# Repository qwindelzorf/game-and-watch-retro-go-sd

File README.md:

# Nintendo® Game & Watch™ Retro-Go SD

A comprehensive emulator collection for the Nintendo® Game & Watch™ with SD Card support, allowing you to play your favorite retro games on the go!

## Table of Contents
- [Support Development](#support-development)
- [Features](#features)
- [SD Card KiCad Project]
- [Installation](#installation)
  - [Pre-modded Options](#pre-modded-options)
  - [Hardware Requirements](#hardware-requirements)
  - [Installation Steps](#installation-steps)
  - [Shell Replacement](#shell-replacement)
  - [Retro-Go-SD Update Steps](#retro-go-sd-update-steps)
- [Supported Systems](#supported-systems)
  - [Emulators](#emulators)
  - [SNES Ports](#snes-ports)
  - [Homebrew Ports](#homebrew-ports)
- [Controls](#controls)
  - [Button Mappings](#button-mappings)
  - [Macros](#macros)
- [Troubleshooting / FAQ](#troubleshooting--faq)
- [Cheat Codes](#cheat-codes)
  - [Cheat codes on NES System](#cheat-codes-on-nes-system)
  - [Cheat codes on GB System](#cheat-codes-on-gb-system)
  - [Cheat codes on PCE System](#cheat-codes-on-pce-system)
  - [Cheat codes on MSX System](#cheat-codes-on-msx-system)
- [NES Emulator](#nes-emulator)
- [MSX Emulator](#msx-emulator)
- [Amstrad CPC6128 Emulator](#amstrad-cpc6128-emulator)
- [Pokémon Mini Emulator](#pokémon-mini-emulator)
- [Homebrew ports](#homebrew-ports)
  - [The Legend of Zelda: A Link to the Past](#the-legend-of-zelda-a-link-to-the-past)
    - [Alternate languages](#alternate-languages)
  - [Super Mario World](#super-mario-world)
  - [Celeste Classic](#celeste-classic)
- [Discord, support and discussion](#discord-support-and-discussion)
- [License](#license)

## Support Development

You can support the development by donating via [PayPal](https://paypal.me/revlys)

## Features

- 🎮 Support for multiple retro gaming systems
- 💾 SD Card storage for ROMs and games
- 💾 4 save state slots per game
- 🎨 Cover art support
- 🔄 Easy firmware updates
- 🌐 Unicode support (Latin and Cyrillic, more to come)
- 🎯 Cheat code support for multiple systems
- 🔄 Dual boot capability (original firmware preservation)

Current limitations :
- Up to 1000 roms/disks will be visible for each system
- CJK characters not yet visible

## SD Card KiCad Project

This is a remake of the original GnW SD Adapter based on the gerbers from the [upstream repo](https://github.com/sylverb/game-and-watch-retro-go-sd/raw/refs/heads/main/assets/GnW_SD_v2.zip). Parts have been changed and the board redesigned for easy production from JLCpcb. 
Credits to Tim Schuerewegen for initial version and hundshamer for updates to make it easier to install.

## Installation

### Pre-modded Options

If you prefer professional installation, contact:
- **Europe**: Sylver ([u/Sylver7667](https://www.reddit.com/user/Sylver7667/) on Reddit, sylver__ on Discord)
- **USA**: hundshamer ([u/hundshamer](https://www.reddit.com/user/hundshamer/) on Reddit)

### Hardware Requirements

To install the hardware mod, you need:

- SD Card flex PCB adapter [SD Card KiCad Project] which can be ordered complete from JLCpcb
- 1x MX25U51245GZ4I00 (64MB SPI flash 1.8v) or bigger

### Installation Steps

1. **Original Firmware Backup / Unlock**
   - Install [gnwmanager](https://github.com/BrianPugh/gnwmanager), follow [installation instructions](https://github.com/BrianPugh/gnwmanager/blob/main/tutorials/installation.md)
   - Connect your JTAG device (ST-Link v2 or others supported devices)
   - Run `gnwmanager unlock` to backup and unlock the console. Follow instructions on computer's screen with attention.
   - If you already have a backup, use `gnwmanager unlock --no-backup` to skip the backup steps

2. **Flash Chip Installation**
   - Install the MX25U51245GZ4I00 flash chip, follow instructions in [this video](https://www.youtube.com/watch?v=mYvK7LyHh1Y) if needed

3. **Patched OFW / Bootloader Installation**
   - For dual boot (recommended):
     ```bash
     gnwmanager flash-patch zelda internal_flash_backup_zelda.bin flash_backup_zelda.bin --bootloader
     ```
   - Without dual boot (not recommended but could help troubleshooting issues if dual boot fails to install):
     ```bash
     gnwmanager flash-bootloader bank1
     ```

   - You can now use bootloader to check that your flash chip is correctly installed. Power on the console (and press GAME+Left if patched OFW is installed) to run the bootloader. You should see a screen like this:

      > Note: If you installed the recommended 64MB chip, you should see "MX25U51245G (64MB)" on the screen.

4. **SD Card Mod Installation**   
   Check this great install video by NaGa :

5. **Retro-Go-SD Installation**
   - Format micro SD card as exFAT (recommended) or FAT32
   - Download latest `retro-go_update.bin` from [releases page](https://github.com/sylverb/game-and-watch-retro-go-sd/releases/latest)
   - Place the file in the root folder of your SD card
   - Insert SD card and start the console

   - You can start filling the created folders on your sd card with uncompressed roms (in /roms/gb, roms/gbc, roms/nes, ...)

### Shell Replacement
   For people who do not want to cut their original shell, Aradia (on Discord) has designed a replacement back shell with SD card access.
   Note that this shell is designed for the GnW_SD_v2.zip version of the flex cable (the one provided earlier on this page)
   The 3D printable file can be downloaded [here](https://github.com/sylverb/game-and-watch-retro-go-sd/raw/refs/heads/main/assets/GnW_Zelda_back_shell.stl).

### Retro-Go-SD Update Steps

   When there is a new Retro-Go-SD release available on github, to install it, just proceed as described :
   - Download latest `retro-go_update.bin` from [releases page](https://github.com/sylverb/game-and-watch-retro-go-sd/releases/latest)
   - Place the file in the root folder of your SD card
   - Insert SD card and start the console
   - Once the update is done, you are ready to use new version

## Tools

### Cover Art Generator (gencovers.py)

Due to memory and power constrains of the Game & Watch hardware, it's not possible to use full size png/jpg/bmp images for cover art.

The `tools/gencovers.py` script helps you generate cover art thumbnails for your games. It can process individual images or batch process all images in a directory.

Note that you will have to run `python3 -m pip install -r requirements.txt` once to install dependencies required by the script.

#### Usage

**Process a single image:**
```bash
python tools/gencovers.py --image /path/to/image.png
# Creates image.img in the same directory

python tools/gencovers.py --image /path/to/image.png --output /path/to/output.img
# Creates the .img file at the specified location
```

**Batch process all images in a directory:**
```bash
python tools/gencovers.py --src roms --dst covers
# Processes all images in the 'roms' directory and creates thumbnails in 'covers'
```

#### Options

- `--image`: Path to a single image file to process (PNG, JPG, JPEG, BMP)
- `--output`: Output path for the single image (only used with --image)
- `--src`: Source directory for batch processing (default: "roms")
- `--dst`: Destination directory for batch processing (default: "covers")
- `--width`: Thumbnail width (default: 128)
- `--height`: Thumbnail height (default: None, uses width-based scaling)
- `--jpg_quality`: JPEG quality 0-100 (default: 85)

The script automatically resizes images to fit within 186x100 pixels while maintaining aspect ratio, and saves them as optimized JPEG files with the `.img` extension.

The `.img` files have to be stored in the /covers folder of your sd card : for the game `/roms/msx/Aleste.rom`, the cover file should be `/covers/msx/Aleste.img`.

## Supported Systems

### Emulators
- Amstrad CPC6128 (beta)
- Atari 2600
- Atari 7800
- ColecoVision
- Gameboy / Gameboy Color
- Game & Watch / LCD Games
- MSX1/2/2+
- Nintendo Entertainment System
- PC Engine / TurboGrafx-16
- Pokémon Mini
- Sega Game Gear
- Sega Genesis / Megadrive
- Sega Master System
- Sega SG-1000
- Tamagotchi P1
- Watara Supervision

### SNES Ports
- The Legend of Zelda: A Link to the Past
- Super Mario World

### Homebrew Ports
- Celeste Classic

## Controls

### Button Mappings
- `GAME` → `START`
- `TIME` → `SELECT`
- `PAUSE/SET` → Emulator menu

### Macros
| Button combination    | Action                                                                 |
| --------------------- | ---------------------------------------------------------------------- |
| `PAUSE/SET` + `GAME`  | Store a screenshot (Disabled by default on 1MB flash builds)          |
| `PAUSE/SET` + `TIME`  | Toggle speedup (1x/1.5x)                                               |
| `PAUSE/SET` + `UP`    | Brightness up                                                          |
| `PAUSE/SET` + `DOWN`  | Brightness down                                                        |
| `PAUSE/SET` + `RIGHT` | Volume up                                                              |
| `PAUSE/SET` + `LEFT`  | Volume down                                                            |
| `PAUSE/SET` + `B`     | Load state                                                             |
| `PAUSE/SET` + `A`     | Save state                                                             |
| `PAUSE/SET` + `POWER` | Poweroff without save-state                                            |

## Troubleshooting

- Bootloader as a diagnostic menu, you can show it by booting with PAUSE/SET button pressed at startup.
- If a savestate is causing crash when power on the console, boot with TIME button pressed to force system to boot in games list menu.

## FAQ

- I'd like to play Zelda 3 in French/Italian/German/... How to change language ?

   First follow the steps to create a zelda3_assets.dat file including wanted languages.
   Load Zelda 3, press Pause/Set button to enter menu, select Options, select Language line and press left/right to change current language. Text for Player Select/Create/... is always in English, but dialogs will be in selected language. Do not change language when a dialog is shown on the screen, it can cause some issues.

- Can you add [new system name] support ?

   Maybe ... Probably not ! G&W system is very limited, it has only about 1MB of RAM free for code + dynamic ressources for each emulator. Most of the time emulators have to be deeply optimized to reduce their memory use so they can fit. Each emulator port is a challenge and some have failed already (fake-08, picodrive, ...).

## Cheat codes

Note: Currently cheat codes are only working with GB, GBC, NES, PCE and MSX games.

To enable, add CHEAT_CODES=1 to your make command. If you have already compiled without CHEAT_CODES=1, I recommend running make clean first.
To enable or disable cheats, select a game then select "Cheat Codes". You will be able to select cheats you want to enable/disable. Then you can start/resume a game and selected cheats will be applied.
On GB, GBC and MSX systems, you can enable/disable cheats during game.

### Cheat codes on NES System

To add Game Genie codes, create a file ending in .ggcodes in the /cheats/nes/ directory with the same name as your rom. For instance, for
"/roms/nes/Super Mario Bros.nes" make a file called "/cheats/nes/Super Mario Bros.ggcodes". In that file, each line can have up to 3 Game Genie codes and a maximum
of 16 lines of active codes (for a max of 3 x 16 = 48 codes). Each line can also have a description (up to 25 characters long).
You can comment out a line by prefixing with # or //. For example:
```
SXIOPO, Inf lives
APZLGG+APZLTG+GAZUAG, Mega jump
YSAOPE+YEAOZA+YEAPYA, Start on World 8-1
YSAOPE+YEAOZA+LXAPYA, Start on World -1
GOZSXX, Invincibility
# TVVOAE, Circus music
```
You can enable / disable each of your codes in the game selection screen.

A collection of codes can be found [here](https://github.com/martaaay/game-and-watch-retro-go-game-genie-codes).

### Cheat codes on GB System

To add Game Genie/Game Shark codes, create a file ending in .ggcodes in the /cheats/gb/ or /cheats/gbc/ directory with the same name as your rom. For instance, for
"/roms/gb/Wario Land 3.gb" make a file called "/cheats/gb/Wario Land 3.ggcodes". In that file, each line can have several Game Genie / Game Shark codes
(separate them using a +) and a maximum of 16 lines of active codes. Each line can also have a description (up to 25 characters long).
You can comment out a line by prefixing with # or //. For example:
```
SXIOPO, Inf lives
APZLGG+APZLTG+GAZUAG, Mega jump
YSAOPE+YEAOZA+YEAPYA, Start on World 8-1
YSAOPE+YEAOZA+LXAPYA, Start on World -1
GOZSXX, Invincibility
# TVVOAE, Circus music
```
You can enable / disable each of your codes in the game selection screen or during game.

### Cheat codes on PCE System

Now you can define rom patch for PCE Roms. You can found patch info from [Here](https://krikzz.com/forum/index.php?topic=1004.0).
To add PCE rom patcher, create a file ending in .pceplus in the /cheats/pce/ directory with the same name as your rom. For instance, for
"/roms/pce/1943 Kai (J).pce" make a file called "/cheats/pce/1943 Kai (J).pceplus".
A collection of codes file can be found [here](https://github.com/olderzeus/game-genie-codes-nes/tree/master/pceplus).

Each line of pceplus is defined as:
```
01822fbd,018330bd,0188fcbd,	Hacked Version
[patchcommand],[...], patch desc

```

Each patch command is a hex string defined as:
```
01822fbd
_
|how much byte to patched
 _____
   |patch start address, subtract pce rom header size if had.
      __...
       |bytes data to patched from start address

```
### Cheat codes on MSX System

You can use blueMSX MCF cheat files with your Game & Watch. A nice collection of patch files is available [Here](http://bluemsx.msxblue.com/rel_download/Cheats.zip).
Just copy the wanted MCF files in the /cheats/msx/ folder with the same name as the corresponding rom/dsk file.
On MSX system, you can enable/disable cheats while playing. Just press the Pause/Set button and choose "Cheat Codes" menu to choose which cheats you want to enable or disable.

## NES Emulator

NES emulation was done using nofrendo-go emulator, it doesn't have the best compatibility but has good performances.
To handle eveything that is not or badly emulated by nofrendo, fceumm emulator has been ported too.
fceumm has very good compatibility but it's using more CPU power, currently about 65-85% of CPU depending on games, disks games (FDS) are taking even more CPU power (about 95%).
Due to the large amount of mappers supported by fceumm, it's not possible to embbed all mappers codes in the G&W memory, so the parsing proccess is listing mappers used by games in the rom/nes folder so only needed mappers are loaded in the G&W. If you are using too much different mappers in the games you have selected, you will have runtime problems. The maximum number of mappers you can use will depends on embedded mappers, but basically it should fit most needs.

Mappers compatibility is basically the same as fceumm version from 01/01/2023. Testing all mappers is not possible, so some mappers that could try to allocate too much ram will probably crash. If you find any mapper that crash, please report on discord support, or by opening a ticket on github.

As Game & Watch CPU is not able to emulate YM2413 at 48kHz, mapper 85 (VRC-7) sound will play at 18kHz instead of 48kHz.

FDS support requires you to put the FDS firmware in `/bios/nes/disksys.rom` file

Note that you can force nofrendo-go usage instead of fceumm by adding FORCE_NOFRENDO=1 option in your make command

## MSX Emulator

MSX system is a computer with a keyboard and with multiple extensions possible (like sound cartridges).
The system needs bios files to be in the roms/msx_bios folder. Check roms/msx_bios/README.md file for details.

What is supported :
- MSX1/2/2+ system are supported. MSX Turbo-R will probably not work on the G&W.
- ROM cartridges images : roms have to be named with rom, mx1 or mx2 extension.
- Disks images : disks images have to be named with dsk extension. Multiple disks games are supported and user can change the current disk using the "Pause/Options/Change Dsk" menu.
- Cheat codes support (MCF files in old or new format as described [Here](http://www.msxblue.com/manual/trainermcf_c.htm))
- The file roms/msx_bios/msxromdb.xml contains control profiles for some games, it allows to configure controls in the best way for some games. If a game has no control profile defined in msxromdb.xml, then controls will be configured as joystick emulation mode.
- Sometimes games require the user to enter his name using the keyboard, and some games like Metal Gear 1/2 are using F1-F5 keys to acces items/radio/... menus. It is possible to virtually press these keys using the "Pause/Options/Press Key" menu.

Note that the MSX support is done using blueMsx 2.8.2, any game that is not working correctly using this emulator will not work on the Game & Watch. To fit in the G&W, a some features have been removed, so it's possible that some games running on blueMSX will not work in the G&W port. The emulator port is still in progress, consider it as a preview version.

## Amstrad CPC6128 Emulator

Amstrad CPC6128 system is a computer with a keyboard and disk drive.

What is supported :
- Amstrad CPC6128 system is the only supported system. CPC464 could be added if there is any interest in doing this. Note that CPC464+/6128+ systems are not supported (running a around 40% of their normal speed so it has been removed)
- Disks images : disks images have to be named with dsk extension. Due to memory constraints, disks images are read only. Multiple disks games are supported and user can change the current disk using the "Pause/Options/Change Dsk" menu.  Both standard and extended dsk format are supported.
- Normally when the amstrad system starts, it will wait the user to enter a run"file or |CPM command to load the content of the disk. As it's not very friendly, the emulator is detecting the name of the file to run and enter automatically the right command at startup
- Sometimes games require the user to enter his name using the keyboard. It is possible to virtually press these keys using the "Pause/Options/Press Key" menu.
- Amstrad screen resolution is 384x272 pixels while G&W resolution is 320x240. The standard screen mode (with no scaling) will show the screen without the borders which will be ok in most cases, but in some cases games are using borders to show some content. If you want to see the whole Amstrad screen on the G&W, set options/scaling to "fit".

Tape support has not been ported, if there is any interest in adding this, it could be considered.

Note that the Amstrad CPC6128 support is done using caprice32 emulator, any game that is not working correctly using this emulator will not work on the Game & Watch. To fit in the G&W, a some features have been removed, so it's possible that some games running on caprice32 will not work in the G&W port. The emulator port is still in progress, consider it as a preview version.

## Vectrex/Odyssey2 Emulator (not included in SD Card version yet)
Vectrex/Odyssey2 is provided by a modified version of o2em emulator.
Support is currently in development so it's unstable, has lots of bugs and it's not really playable.
To play, you need a bios file, for now rename your bios file to bios.bin and put it in the roms/vectrex folder

# Pokémon Mini Emulator
https://github.com/libretro/PokeMini was used for porting. You can provide a bios file in /bios/mini/bios.min file, but it's optional : if no bios file is provided, an integrated open source bios will be used.

## Homebrew ports

Some homebrew/SNES games have been _ported_ to the G&W.

### The Legend of Zelda: A Link to the Past

To play The Legend of Zelda: A Link to the Past, you need to generate the zelda3_assets.dat file by following these steps :
- clone the project with submodules if not already done :
```git clone --recurse-submodules https://github.com/sylverb/game-and-watch-retro-go-sd```
- install python requirements : ```python3 -m pip install -r requirements.txt```
- copy zelda3.sfc (USA version, sha1 = '6d4f10a8b10e10dbe624cb23cf03b88bb8252973') rom to external/zelda3/tables/
- run 'make -C external/zelda3 tables/zelda3_assets.dat' command

The file zelda3_assets.dat will be created in external/zelda3/tables. Copy the zelda3_assets.dat file in /roms/homebrew/ folder of your sd card.

If you want to create zelda3_assets.dat file with several languages, the steps are :
- copy all zelda3_xx.sfc files (including us zelda3.sfc) from languages you want to include (check names and sha1 below)
- go in tables folder : 'cd external/zelda3/tables'
- for each rom run this command : 'python3 restool.py --extract-dialogue -r ./zelda3_xx.sfc' (replace _xx with real rom names)
- run the command to build assets file : 'python3 restool.py --extract-from-rom --languages=fr,fr-c,de,en,es,pl,pt,nl' (adapt the languages list to fit the languages you did provide)

The file zelda3_assets.dat will be created in external/zelda3/tables. Copy the zelda3_assets.dat file in /roms/homebrew/ folder of your sd card.

When playing, you'll be able to change current language by going in the options menu.

Due to the limited set of buttons (especially on the Mario console), the controls are peculiar:

| Description | Binding on Mario units | Binding on Zelda units |
| ----------- | ---------------------- | ---------------------- |
| `A` button (Pegasus Boots / Interacting) | `A` | `A` |
| `B` button (Sword) | `B` | `B` |
| `X` button (Show Map) | `GAME + B` | `TIME` |
| `Y` button (Use Item) | `TIME` | `SELECT` |
| `Select` button (Save Screen) | `GAME + TIME` | `GAME + TIME` |
| `Start` button (Item Selection Screen) | `GAME + A` | `START` |
| `L` button (Quick-swapping, if enabled) | `-` | `GAME + B` |
| `R` button (Quick-swapping, if enabled) | `-` | `GAME + A` |

Some features can be configured with flags:

| Build flag    | Description |
| ------------- | ------------- |
| `LIMIT_30FPS` | Limit to 30 fps for improved stability.<br>Enabled by default.<br>Disabling this flag will result in unsteady framerate and stuttering. |
| `FASTER_UI` | Increase UI speed (item menu, etc.).<br>Enabled by default. |
| `BATTERY_INDICATOR` | Display battery indicator in item menu.<br>Enabled by default. |
| `FEATURE_SWITCH_LR` | Item switch on L/R. Also allows reordering of items in inventory by pressing Y+direction.<br>Hold X, L, or R inside of the item selection screen to assign items to those buttons.<br>If X is reassigned, Select opens the map. Push Select while paused to save or quit.<br>When L or R are assigned items, those buttons will no longer cycle items. |
| `FEATURE_TURN_WHILE_DASHING` | Allow turning while dashing. |
| `FEATURE_MIRROR_TO_DARK_WORLD` | Allow mirror to be used to warp to the Dark World. |
| `FEATURE_COLLECT_ITEMS_WITH_SWORD` | Collect items (like hearts) with sword instead of having to touch them. |
| `FEATURE_BREAK_POTS_WITH_SWORD` | Level 2-4 sword can be used to break pots. |
| `FEATURE_DISABLE_LOW_HEALTH_BEEP` | Disable the low health beep. |
| `FEATURE_SKIP_INTRO_ON_KEYPRESS` | Avoid waiting too much at the start.<br>Enabled by default. |
| `FEATURE_SHOW_MAX_ITEMS_IN_YELLOW` | Display max rupees/bombs/arrows with orange/yellow color. |
| `FEATURE_MORE_ACTIVE_BOMBS` | Allows up to four bombs active at a time instead of two. |
| `FEATURE_CARRY_MORE_RUPEES` | Can carry 9999 rupees instead of 999. |
| `FEATURE_MISC_BUG_FIXES` | Enable various zelda bug fixes. |
| `FEATURE_CANCEL_BIRD_TRAVEL` | Allow bird travel to be cancelled by hitting the X key. |
| `FEATURE_GAME_CHANGING_BUG_FIXES` | Enable some more advanced zelda bugfixes that change game behavior. |
| `FEATURE_SWITCH_LR_LIMIT` | Enable this to limit the ItemSwitchLR item cycling to the first 4 items. |

#### Alternate languages

By default, dialogues extracted from the US ROM are in english. You can replace dialogues with another language by using a localized ROM file. Supported alternate languages are:

| Language | Origin | Naming | SHA1 hash |
| -------- | ------ | ------ | --------- |
| German   | Original | zelda3_de.sfc | 2E62494967FB0AFDF5DA1635607F9641DF7C6559 |
| French   | Original | zelda3_fr.sfc | 229364A1B92A05167CD38609B1AA98F7041987CC |
| French (Canada) | Original | zelda3_fr-c.sfc | C1C6C7F76FFF936C534FF11F87A54162FC0AA100 |
| English (Europe) | Original | zelda3_en.sfc | 7C073A222569B9B8E8CA5FCB5DFEC3B5E31DA895 |
| Spanish  | Romhack | zelda3_es.sfc | 461FCBD700D1332009C0E85A7A136E2A8E4B111E |
| Polish   | Romhack | zelda3_pl.sfc | 3C4D605EEFDA1D76F101965138F238476655B11D |
| Portuguese | Romhack | zelda3_pt.sfc | D0D09ED41F9C373FE6AFDCCAFBF0DA8C88D3D90D |
| Dutch    | Romhack | zelda3_nl.sfc | FA8ADFDBA2697C9A54D583A1284A22AC764C7637 |
| Swedish  | Romhack | zelda3_sv.sfc | 43CD3438469B2C3FE879EA2F410B3EF3CB3F1CA4 |

### Super Mario World

To play Super Mario world you need to copy the smw_assets.dat file in /roms/homebrew/ folder of your sd card.
the smw_assets.dat file can be generated by doing the following steps :
- clone the project with submodules if not already done :
```git clone --recurse-submodules https://github.com/sylverb/game-and-watch-retro-go-sd```
- install python requirements : ```python3 -m pip install -r requirements.txt```
- copy smw.sfc (USA version, sha1 = '6B47BB75D16514B6A476AA0C73A683A2A4C18765') rom to external/smw/assets/
- run 'make -C external/smw smw_assets.dat' command
The file smw_assets.dat will be created in external/smw.

Due to the limited set of buttons (especially on the Mario console), the controls are peculiar:

| Description | Binding on Mario units | Binding on Zelda units |
| ----------- | ---------------------- | ---------------------- |
| `A` button (Spin Jump) | `GAME + A` | `SELECT` |
| `B` button (Regular Jump) | `A` | `A` |
| `X`/`Y` button (Dash/Shoot) | `B` | `B` |
| `Select` button (Use Reserve Item) | `TIME` | `TIME` |
| `Start` button (Pause Game) | `GAME + TIME` | `START` |
| `L` button (Scroll Screen Left) | `-` | `GAME + B` |
| `R` button (Scroll Screen Right) | `-` | `GAME + A` |

Some features can be configured with flags:

| Build flag    | Description |
| ------------- | ------------- |
| `LIMIT_30FPS` | Limit to 30 fps for improved stability.<br>Enabled by default.<br>Disabling this flag will result in unsteady framerate and stuttering. |

### Celeste Classic

This is a port of the Pico-8 version of Celeste Classic. Not a Pico-8 emulator.

## Discord, support and discussion 

Please join the [Discord](https://discord.gg/vVcwrrHTNJ).

## License

This project is licensed under the GPLv2. Some components are available under the MIT license. Respective copyrights apply to each component.

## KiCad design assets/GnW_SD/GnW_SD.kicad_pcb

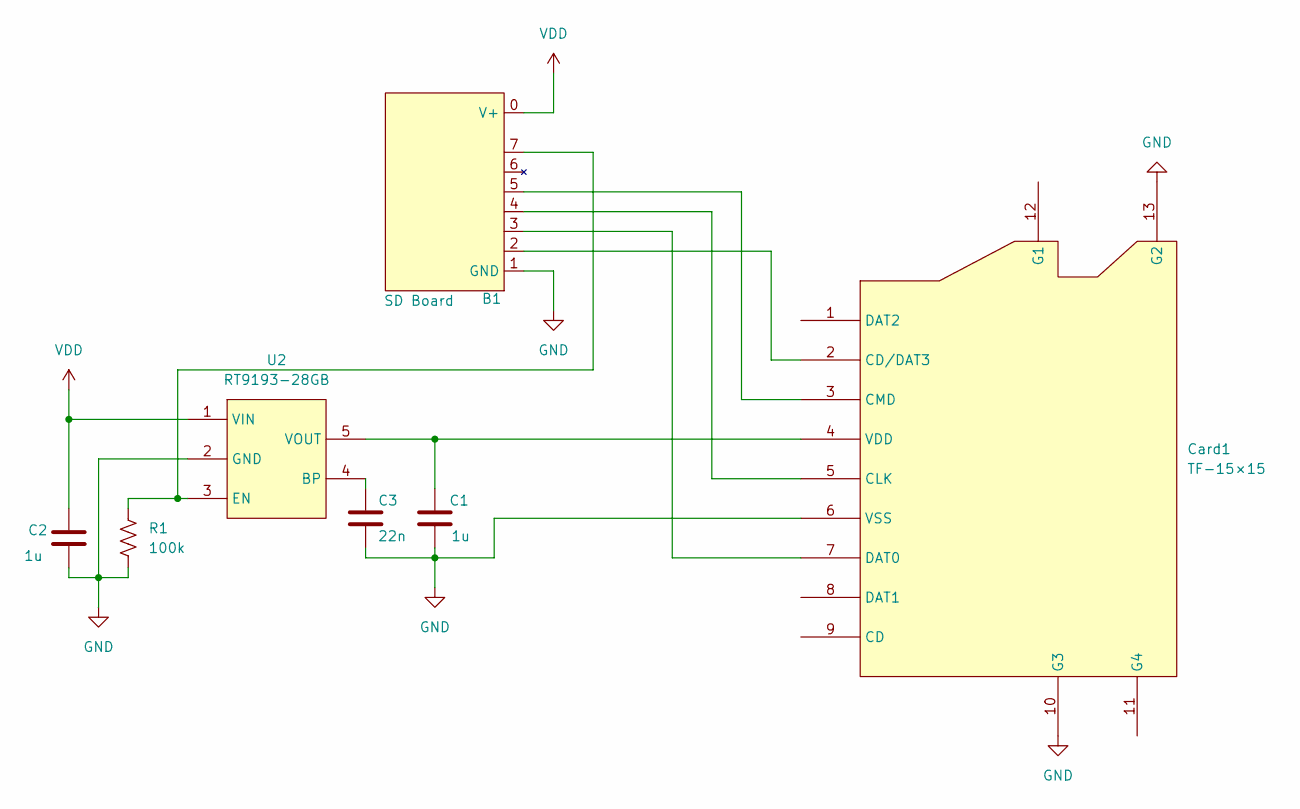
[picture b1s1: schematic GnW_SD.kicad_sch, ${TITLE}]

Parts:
B1: SD Board; Board
C1, C2: 1u; C_0805_2012Metric; LCSC C28323
C3: 22n; C_0805_2012Metric; LCSC C1729
Card1: TF-15×15; TF-SMD_TF-15-15; LCSC Part C111196
R1: 100k; R_0805_2012Metric; LCSC C25611
U2: RT9193-28GB; SOT-23-5_L3.0-W1.7-P0.95-LS2.8-BR; LCSC Part C56731

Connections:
GND: B1.1 (GND), C1.2, C2.2, C3.2, Card1.6 (VSS), Card1.10 (G3), Card1.13 (G2), R1.2, U2.2 (GND)
unnamed: B1.2, Card1.2 (CD/DAT3)
unnamed: B1.4, Card1.5 (CLK)
unnamed: B1.5, Card1.3 (CMD)
unnamed: B1.3, Card1.7 (DAT0)
unnamed: C1.1, Card1.4 (VDD), U2.5 (VOUT)
unnamed: C3.1, U2.4 (BP)
unnamed: B1.7, R1.1, U2.3 (EN)
VDD: B1.0 (V+), C2.1, U2.1 (VIN)

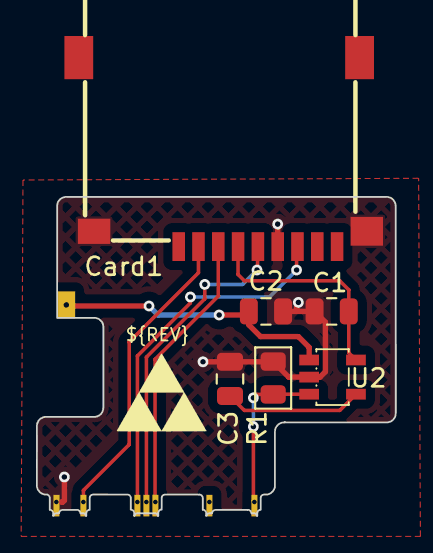
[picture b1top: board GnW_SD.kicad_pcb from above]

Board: 2 copper layers, 19.9 x 17.7 mm, 8 parts (1 on the bottom side), 9 nets.

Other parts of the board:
Q**: Qwindelzorf; qwindelzorf_1520

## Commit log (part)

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2024-08-30 Add missing a2600 rom folder
2024-08-30 Remove littlefs and tamp
2024-09-01 Add spi1 configuration for sd-card and FatFS (untested)
2024-09-08 Fix SD card init + add deinit
2024-09-09 Removal of build/config rependency as it's not needed anymore Add support for dynamic parsing of sd card /roms folders
2024-09-12 Various updates (compression support removal from most emulators)
2024-09-13 Fix system not correctly detected when starting game. Do not load rom in flash for homebrews
2024-09-14 Handle byte swapping of rom data for genesys emulator
2024-09-15 add wrapper to allow use standard posix files functions add crc32 computing for systems needing it (with cache system) create needed folders at startup
2024-09-15 SMS/GG : use cached CRC32 is existing
2024-09-16 Add sha1 hw computing for future use
2024-09-16 Add NES support (with nofrendo-go only for now)
2024-09-16 Check flash content to program it only if needed
2024-09-21 Preliminar implementation of savestate (4 slots and preview image)
2024-09-22 Fill not visible buffer with preview then copy it to current buffer for almost instant display
2024-09-22 Automatically quit save delete menu if there are no saves left
2024-09-24 Fix some potential watchdog trigger
2024-09-24 Improvement of SD Card detection and communication code Added SD_CARD parameter with following values : - 0 : use tinyfs on internal flash to store data (not ready yet) - 1 : use SD Card reader on sp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
2024-09-24 Add softspi code for sd card on qspi port
2024-09-24 Add savestate and screenshot for celeste port
2024-09-24 Fix compilation issue
2024-09-24 Add savestate and screenshot for genesis emulator
2024-09-25 Changed screenshot function callbacks to only fill buffer with data and return buffer address
2024-09-26 Add savestate and screenshot for PC Engine emulator
2024-09-26 Small improvement in save code for tgb_dual
2024-09-30 Minor comments updates
2024-10-01 Preliminar support for yota9's sd card design
2024-10-01 Introduce GNW_DISABLE_COMPRESSION to remove compression support when building system for SD Card. Compression is not really needed when using sd card and it is allowing to save some space in internal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
2024-10-01 Remove save manager
2024-10-01 If building for SD Card reader, only use internal flash, not external
2024-10-01 First design of yota9's pcb seems to not work well when overclocking OSPI clock, keep using lower frequency for this SD Card adapter
2024-10-01 Add block write with softspi
2024-10-02 Add savestate and screenshot for SMS/GG emulator
2024-10-02 Fix possible memory leak in savestate management of GB emulator
2024-10-02 Restored compression code for several emulators
2024-10-02 Add savestate and screenshot for Watara Supervision emulator
2024-10-04 Implement Flash SDPD request to get flash chip size. Added a debug info to present this info to the user
2024-10-05 Remove CI rules for now as it's not working
2024-10-05 Removed some useless comments
2024-10-05 Do not clear framebuffers if loading a savestate as framebuffer is probably filled with a screenshot of the savestate
2024-10-05 Add gw_flash_alloc.h, reformat gw_flash_alloc.c
2024-10-10 Do not disable OSPI1 IRQ for OSPI1 sd card as it's not needed
2024-10-10 Do not use external flash for code anymore when building with SD Card support Create emulators core files in build/cores folder use "make flash_sd" to flash internal flash and load cores files to sd 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
2024-10-11 Set head_size back to 32KB
2024-10-11 Enable all working emulators, some minor updates
2024-10-11 Flash allocator : fix issues with invalidation of overwritten files
2024-10-11 Add missing file name shown in status bar
2024-10-12 Remove file extension in the game name
2024-10-12 Add celeste homebrew copy
2024-10-13 Use 3 cache buffer for logos, one for general logos, one for headers and one for pads. It'll allow to keep smooth rom selection by not reading data from SD Card at each screen refresh
2024-10-15 Add support for covers. Files shall be jpg files, less than 10KB, typical size of 96*128 pixels. Covers shall be named like /covers/gb/game.gb.img /covers/nes/game.nes.img ...
2024-10-15 Proper jpeg/covers buffers size
2024-10-17 Add savestates for NES Nofrendo emulator
2024-10-18 remove SD_CARD=2 for ospi1 SD Card, SD Card type is now detected at startup if SD_CARD=1
2024-10-19 Remove image file size info from properties
2024-10-28 Preliminar support for MSX games (rom/dsk)
2024-10-29 Proper memory management for file extension field
2024-10-29 MSX : add savestates & screenshot
2024-10-29 MSX : copy roms in flash but not dsk files
2024-11-01 MSX : get sha1 of game file and get game data (mapper, ...) from a compact database file.
2024-11-01 Add proper python header to binary_rgb565_to_png.py
2024-11-07 Remove intflash 2 references in ld file
2024-11-21 cleanup of sd card ld file
2024-11-28 NES fceumm : Only load needed mapper in ram. This allows to compile and link all supported mappers. Each mapper is stored in a separated file, a database allows to now which mapper file to load depen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
2024-11-28 NES : removed useless #if / #endif related to nofrendo
2024-11-30 NES : add NSF dynamic mapper loading
2024-11-30 Makefile sd_flash : copy nes mappers table in sd card
2024-12-02 NES : Add support for ines corrected header data in fceumm-go
2024-12-05 NES - FCEUMM : color palettes are stored in a file in /bios/nes folder
2024-12-11 Add some watchdog refresh to prevent possible crash in some cases Fix issue #12
2024-12-13 Fix first make error
2024-12-14 Covers : do not allocate buffer memory several times (fix #14)
2024-12-21 Add progress bar when caching game in flash (implement #1)
2024-12-22 General : add protections to prevent wrong allocation of memory when ram_start is not initialized
2025-01-09 default value for SD_CARD is now 1 (to enable SD Card support) default value for SINGLE_FONT is now 1 to limit space used by fonts as they are currently stored in internal flash
2025-01-09 Enable exFat support
2025-01-09 TGBDual : ignore pressed key when pause button is pressed as it is used for shortcuts to change volume/contrast/...
2025-01-13 Modified clock configuration to allow changing overclocking setting without rebooting.
2025-01-18 Updated Makefile to copy Celeste binary in the correct place added build_update_archive make command to build update archive
2025-01-18 Add GitHub Actions workflow to generate gw_update.tar
2025-01-18 workflow corrections
2025-01-18 update archive creation command
2025-01-18 update workflow for make command to use available processors to build application
2025-01-20 Use git tag to define version of Retro-Go SD Some cleanup
2025-01-20 When drawing a dialog box, also use title to find correct width of the box
2025-01-21 Renamed make build_update_archive command to release command removed artifact upload from github action when doing a commit
2025-01-21 Fix compilation problem with firmware_update dependency
2025-01-21 Add deliveries to github actions
2025-01-21 Github actions delivery script update
2025-01-22 Firmware update archive is now a single file containing the firmware update application and the firmware update package
2025-01-22 Improved changelog
2025-01-23 Reset settings is now also removing info about cached roms in flash
2025-01-23 Fix minor warning
2025-01-23 Fix core name for Atari 7800 Fix rom finding after a power off/on save
2025-01-23 Atari 7800 : implement savestates and screenshot
2025-01-28 Amstrad : Add support of savestates on sd card
2025-01-28 Changelog for v0.1.0
2025-01-28 Preliminar update of readme for sd card support
2025-02-04 - Text that spans multiple lines is now correctly handled (Fix #19)
2025-02-05 Covers : fix issue if cover was not 128x96 pixels to prevent issues in some coverflow modes, keep all covers for a given system the same size
2025-02-05 Fix memory allocation overflow when having a lot of roms in all systems
2025-02-13 Removed useless files & logs
2025-02-13 Add Super Mario World port support
2025-02-13 Update firmware update software to fix some potential issues
2025-02-17 Firmware update : correctly set extracted files date
2025-02-17 Add support for Zelda 3 A Link To The Past (us language only for now)
2025-02-18 Zelda 3 : fix crash when entering sanctuary add support for language selection in options
2025-02-19 Enable Tamagotchi emulator
2025-02-19 set HDMI-CEC to 0.
2025-02-19 use the external offset stored in HDMI-CEC.
2025-02-19 fix address_in_flash calculation.
2025-02-20 Allow to split gb and gbc roms in /roms/gb and /toms/gbc folder
2025-02-20 Add tools/gencovers.py script to generate covers from png/jpg/...
2025-02-23 Fix for games in /roms/gbc folder not running
2025-02-23 Add support of sram savestates for Super Mario World & Zelda 3
2025-02-23 If the OFW is present, use the RTC backup register to keep booting into retro-go or to choose to return to OFW
2025-02-24 Improve OFW detection
2025-02-24 Changelog for v0.4.3
2025-02-24 It is actually v0.4.2
2025-03-01 Fix memory lead in cheats code management
2025-03-01 Allow to resume game if there only is a sram save present
2025-03-03 Cheats : add save of selected cheats in files (/cheats/.../*.state)
2025-03-03 Firmware update : enable watchdog to prevent locking if an unexpected problem occurs
2025-03-03 Fix error when using multiple blocks reading commands with OSPI SD Card.
2025-03-03 Changelog for v0.5.0
2025-03-08 TGB-Dual : - fix memory allocation issue for cheat codes - add support for game genie codes with '-' included - fix issues with color palettes & added G&W OFW palette
2025-03-11 Add support for some 3.3v flash chips (need hardware mod to provide 3.3v to the chip)
2025-03-11 Changelog for v0.5.1
2025-03-12 Fix regression in GB palettes
2025-03-20 Update Readme file
2025-03-23 Update Readme file, add stl file for back shell
2025-04-01 Add support for Pokémon Mini system
2025-04-02 Pokémon mini : add gfx for header and pad
2025-04-04 Pokémin mini : add options to change settings add a new path file for saving emulators global settings
2025-04-04 README.md update to fix some errors
2025-04-04 MSX : load games <= 128KB in ram instead of caching them in flash
2025-04-09 Load games in ram when possible GB : fix emulation problem in tgbdual (fix Shantae glitches)
2025-04-17 Allow to change disk when needed on MSX and Amstrad
2025-05-02 Remove gnuboy related files, tgb-dual is better now
2025-05-06 Add FAQ entry about Zelda 3 language change
2025-05-15 Changed bilinear filtering to be less blurry (fix by DasBoss)
2025-05-21 Fix issue with flash cache management
2025-05-21 Atari 2600 : Add logos and database management (a2600 not enabled yet due to conflicts with tgbdual)
2025-05-21 add script to creat logo from png file
2025-05-22 Fix linux celeste compilation
2025-05-23 Atari 2600 : - Load roms in ram when possible - Properly handle controllers swap
2025-05-27 Readme : add missing steps dor super mario world/zelda 3 assets files generation
2025-05-31 SMS : Fix savestate crash
2025-06-01 Atari 2600 : Improved music/sound
2025-06-03 Atari 2600 : fix warnings and set proper folder for eeprom files
2025-07-01 Allow to create screenshot in /screenshots folder by pressing GAME+PAUSE
2025-07-05 Use RGB565 BMP for screenshots instead of RGB888
2025-07-05 Fix some errors in BMP header for screenshotsy
2025-07-12 Fix fat/exfat remount issue when exiting a game with some sd card models
2025-07-18 MSX : fix SCC/SCC+ sound for disk games (SD Snatcher/Snatcher/...)
2025-07-18 Fix compilation failure due to latest commit
2025-09-06 NES : fix problem with savestates for some mappers (19, 210, 539)
2025-09-07 MSX : fix missing SCC cartridge insert for some disk games
2025-09-07 Changelog for v0.7.2
2025-09-11 Software is now the same for Mario and Zelda hardware. Model type detection is done by detecting the installed original firmware. If no OFW is installed, it will run as a Zelda unit. There is no need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
2025-09-13 Changelog for v0.8.0
2025-10-27 Rework SD card board

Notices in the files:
README.md:
License:
This project is licensed under the GPLv2. Some components are available under the MIT license. Respective copyrights apply to each component.
